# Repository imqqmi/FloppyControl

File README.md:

# FloppyControl

## Introduction
This project started in 2015. I had 300 floppy disks that I kept from my Amiga 500 and Amiga 1200 period. I planned to buy a second hand Amiga after I sold them for a new PC. That of course didn't happen. The data stored on the floppy disks was mostly my personal files, videos, music modules, painted pictures, 3D objects and renderings etc. And a complete backup of my system and data files. I wanted to reconstruct the files that I used to have. 

However, the Amiga disk format is not something any PC could read, at least not in Windows in a simple way. The disks were in a poor state with fungus and dust. So I set out to clean them. The 3D printable Floppy cleaning kit was a result of this. 

## This is the stategy I followed to get the most data without the risk of losing it:
- The most valuable data will be recovered once I can be certain the recovery proces is sound
- No captured data is thrown away. The first capture could be the best one because the disk may disintegrate/scratch during the capture process due to the disk surface letting loose.
- Extensive analysis is done to make sure that every opportunity is taken to get the data. This includes doing oscilloscope captures of the analoque flux signal, error correct and looking for duplicate data for reconstruction
- Low cost, off the shelve parts
- Windows application to control the hardware (C#)

## Status
This is the first commit of the project. I will call it version 1.0. It's capable of capturing Amiga and PC DOS disks and some variants of both. MSX disks for example are also supported. All disks can be captured, though not all disks can be decoded to a disk image yet. You could try adding your own.

## Hardware
The first version I made was based on a PIC16F1938 overclocked at 80MHz. An USB2RS232 donlge with a PL2303 chip was used at 5mbit/s.
The second (current) version uses a standard Arduino Due. I've designed a shield for it so it can easily be built. The native usb is used which eliminates the USB2RS232 dongle and makes things a lot more stable.

## Software
The real magic happens in the software that converts the flux transitions (or periods) into MFM, then into data and finally into sectors and disk images.

The following disk formats are supported:
- Double density and high density (720KB and 1.44MB) 3.5" disks
- 360KB 5.25" PCDOS disks.
- M2 special format for storing larger amounts of data
- AmigaDOS and Amiga DiskSpare disk formats. PFS is also supported since the format is similar to AmigaDOS.

File formats that can be imported:
- .bin files produces by FloppyControl App, a simple stream dump file format. Each byte contains a period of 2, 4, 6 or 8us. Timer tick frequency may vary.
- .SCP files can be imported
- .raw files from Kryoflux can be imported.

There are some experimental error correction functions in FloppyControl that allows you to do some analysis and limited error correction. It's still a very time consuming and manual process.

Other features include:
- Oscilloscope analogue flux transition capture support. At this point only the Rigol DS1054Z is supported and tested. Other scopes may work but it's not tested. Please let me know if it works. A modified floppy drive is needed for this. The oscilloscope should have at least 20MB storage to store a full track in memory.
- Oscilloscope captures can be edited so that errors can be corrected manually. A waveform editor is included. 
- The waveform can be converted into sector data using the processing capabilities (differential filtering, time based filtering, period conversion and data conversion).
- A sectormap shows you exactly the state of the capture and conversion. Bad sectors can be recaptured and existing data can be reprocessed with different settings, allowing you to 'scan' for good sectors in the dataset.
- All the graphs have some kind of interaction with them. 
  - The histogram can be clicked, this will activate automatic peak detection for the MFM processing. This will find the optimum settings for you.
  - The scatterplot will zoom in and out using the scroll wheel and you can drag to move the view to another location. For PC data, the periods can be edited (enable editing to avoid accidental changes). 
  - The Oscilloscope graphs can likewise be moved and zoomed. It has some advanced scaling routines to display the waveforms like an oscilloscope does, so you can see subpixel detail to find weak spots in the signal easier and faster.
  - The error correction map can be used to locate problem areas by overlaying two captures of the same sector (if the header is crc ok). This may help pinpointing the problem area and allows you to try automatic error correction (using guestimated brute force).
  - Error corrected sectors will be copied to the sector map.
  - There's some rudimentary multi threading support but it breaks in most cases. Try if it works, it'll speed up processing up to 3x on a quad core. 
  - FloppyControl uses a base folder in which the captures are stored. The Base filename is used to create a folder and naming the files inside that folder using a counter. It will never overwrite data (for .bin, .prj and dsk/adf files).
  - bin files with bad sectors can be saved as bad sectors only. This makes them much smaller for reprocessing and finding that illusive good sector.
  - You can choose 'bad sectors only' during processing. This does the same as saving just the bad sectors, it'll reduce the amount of data processed (all good sectors are skipped, they are found already so no point in reprocessing them).

The sources are released as GPL v3.0.

The firmware can be compiled using Arduino Studio v1.8.8.

The project makes use of DPLL class which is based on US patent 4,780,844 and written by DrCoolzic (Jean Louis-Guérin) and gracefully allowed me to inlcude it in this project. See the file DPLL.cs for more information.

The FloppyControl App can be compiled using Visual Studio 2015 or 2017 community edition. You may need to install VC redistributables to run the software as stand alone.

The PCB for the PIC and Arduino Due shield version is created in Eagle v7.3. Newer versions of eagle (free/community edition should work). 

Please let me know if you have any questions. Contributions to the project is appreciated. Please send the pull requests, I'll see if I can integrate them.

## More information

See my blog for more information:
http://www.makercentral.net

See videos about the use of FloppyControl App:
https://www.youtube.com/channel/UCJSWen8mcsrenXGCEr2fJ9w

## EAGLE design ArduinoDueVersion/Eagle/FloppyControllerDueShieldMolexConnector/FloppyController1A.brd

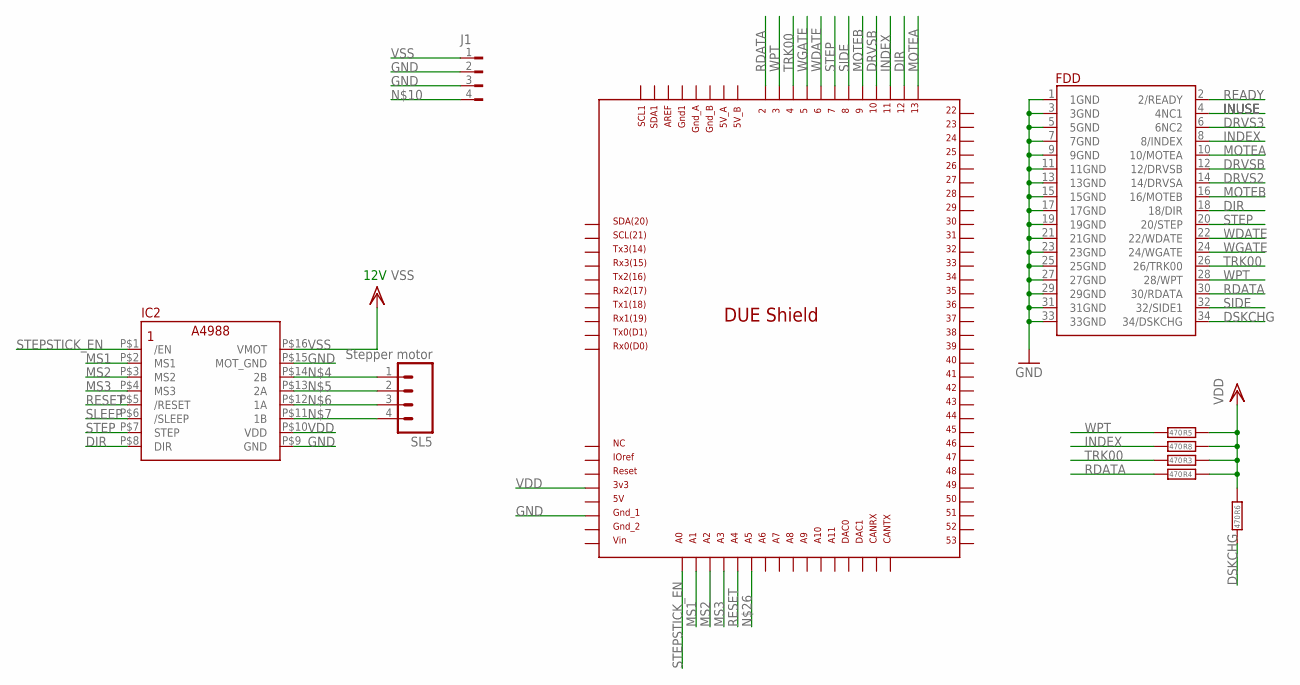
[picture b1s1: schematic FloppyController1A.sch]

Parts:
FDD: FLOPPY_34PIN_CONN; FLOPPY_34PIN_DUALROW
IC2: STEPSTICK_A4988
J1: FLOP-4W827001; 827001
R3, R4, R5, R6, R8: 470; M1206
SL5: Stepper motor; 04P
U$1: DUE(NOCONN); DUE(NORMAL_NO_CONN)

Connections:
DIR: FDD.18 (18/DIR), IC2.P$8 (DIR), U$1.12
DRVS2: FDD.14 (14/DRVSA)
DRVS3: FDD.6 (6NC2)
DRVSB: FDD.12 (12/DRVSB), U$1.10
DSKCHG: FDD.34 (34/DSKCHG), R6.1
GND: FDD.1 (1GND), FDD.3 (3GND), FDD.5 (5GND), FDD.7 (7GND), FDD.9 (9GND), FDD.11 (11GND), FDD.13 (13GND), FDD.15 (15GND), FDD.17 (17GND), FDD.19 (19GND), FDD.21 (21GND), FDD.23 (23GND), FDD.25 (25GND), FDD.27 (27GND), FDD.29 (29GND), FDD.31 (31GND), FDD.33 (33GND), IC2.P$9 (GND), IC2.P$15 (MOT_GND), J1.2, J1.3, U$1.GND_1
INDEX: FDD.8 (8/INDEX), R8.1, U$1.11
INUSE: FDD.4 (4NC1)
MOTEA: FDD.10 (10/MOTEA), U$1.13
MOTEB: FDD.16 (16/MOTEB), U$1.9
MS1: IC2.P$2 (MS1), U$1.A1
MS2: IC2.P$3 (MS2), U$1.A2
MS3: IC2.P$4 (MS3), U$1.A3
unnamed: IC2.P$14 (2B), SL5.1
unnamed: IC2.P$13 (2A), SL5.2
unnamed: IC2.P$12 (1A), SL5.3
unnamed: IC2.P$11 (1B), SL5.4
RDATA: FDD.30 (30/RDATA), R4.1, U$1.2
READY: FDD.2 (2/READY)
RESET: IC2.P$5 (/RESET), U$1.A4
SIDE: FDD.32 (32/SIDE1), U$1.8
SLEEP: IC2.P$6 (/SLEEP)
STEP: FDD.20 (20/STEP), IC2.P$7 (STEP), U$1.7
STEPSTICK_EN: IC2.P$1 (/EN), U$1.A0
TRK00: FDD.26 (26/TRK00), R3.1, U$1.4
VDD: IC2.P$10 (VDD), R3.2, R4.2, R5.2, R6.2, R8.2, U$1.3V3
VSS: IC2.P$16 (VMOT), J1.1
WDATE: FDD.22 (22/WDATE), U$1.6
WGATE: FDD.24 (24/WGATE), U$1.5
WPT: FDD.28 (28/WPT), R5.1, U$1.3

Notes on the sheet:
12V

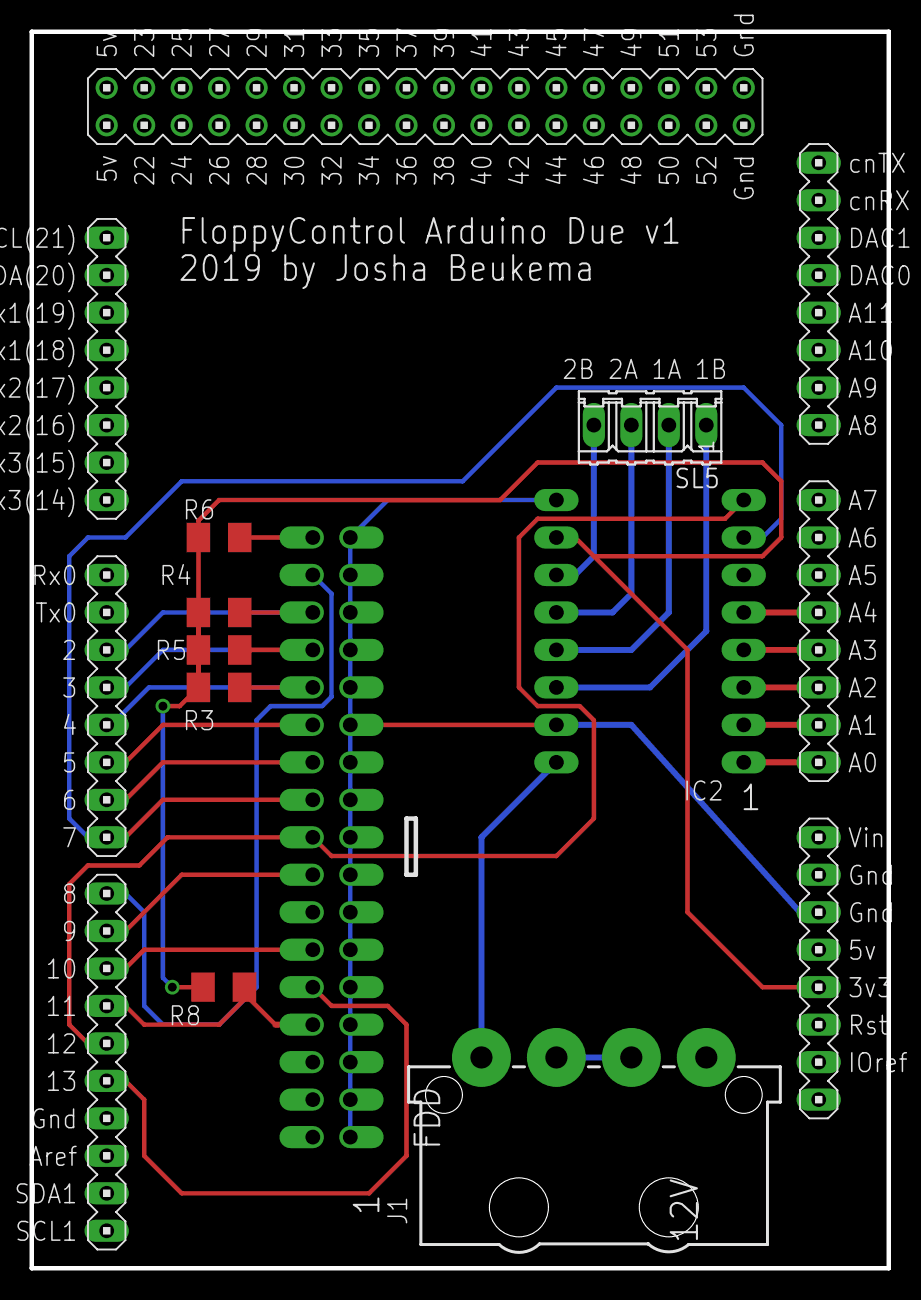
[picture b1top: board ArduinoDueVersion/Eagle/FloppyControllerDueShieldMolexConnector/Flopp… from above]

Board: 2 copper layers, 58.1 x 83.8 mm, 10 parts (0 on the bottom side), 25 nets.

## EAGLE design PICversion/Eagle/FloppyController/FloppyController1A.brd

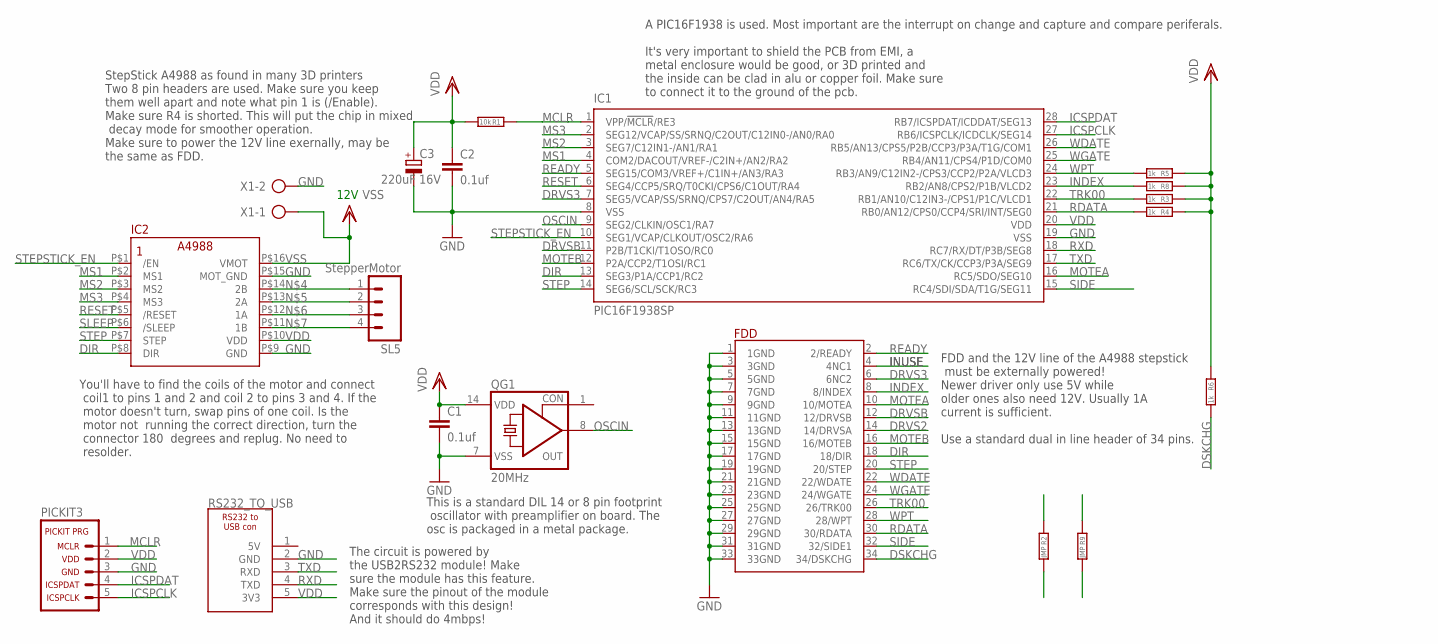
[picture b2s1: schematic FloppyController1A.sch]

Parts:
C1, C2: 0.1uf; C0805TOP
C3: 220uF 16V; E2,5-6
FDD: FLOPPY_34PIN_CONN; FLOPPY_34PIN_DUALROW
IC1: PIC16F1938SP; DIL28-3
IC2: STEPSTICK_A4988
PICKIT3: PICKIT3CONNECTOR; 05P
QG1: 20MHz; SG51
R1: 10k; M1206
R2, R9: JMP; M1206
R3, R4, R5, R6, R8: 1k; M1206
RS232_TO_USB: RS232_TO_USB_CONNECTOR; 05P
SL5: StepperMotor; 04P
X1: AK500/2-H

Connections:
DIR: FDD.18 (18/DIR), IC1.13 (SEG3/P1A/CCP1/RC2), IC2.P$8 (DIR)
DRVS2: FDD.14 (14/DRVSA)
DRVS3: FDD.6 (6NC2), IC1.7 (SEG5/VCAP/SS/SRNQ/CPS7/C2OUT/AN4/RA5)
DRVSB: FDD.12 (12/DRVSB), IC1.11 (P2B/T1CKI/T1OSO/RC0)
DSKCHG: FDD.34 (34/DSKCHG), R6.1
GND: C1.2, C2.2, C3.-, FDD.1 (1GND), FDD.3 (3GND), FDD.5 (5GND), FDD.7 (7GND), FDD.9 (9GND), FDD.11 (11GND), FDD.13 (13GND), FDD.15 (15GND), FDD.17 (17GND), FDD.19 (19GND), FDD.21 (21GND), FDD.23 (23GND), FDD.25 (25GND), FDD.27 (27GND), FDD.29 (29GND), FDD.31 (31GND), FDD.33 (33GND), IC1.8 (VSS), IC1.19 (VSS), IC2.P$9 (GND), IC2.P$15 (MOT_GND), PICKIT3.3 (3_GND), QG1.7 (VSS), R9.1, R9.2, RS232_TO_USB.2 (GND), X1.2
ICSPCLK: IC1.27 (RB6/ICSPCLK/ICDCLK/SEG14), PICKIT3.5 (5_ICSPCLK)
ICSPDAT: IC1.28 (RB7/ICSPDAT/ICDDAT/SEG13), PICKIT3.4 (4_ICSPDAT)
INDEX: FDD.8 (8/INDEX), IC1.23 (RB2/AN8/CPS2/P1B/VLCD2), R8.1
INUSE: FDD.4 (4NC1)
MCLR: IC1.1 (VPP/!MCLR!/RE3), PICKIT3.1 (1_MCLR), R1.2
MOTEA: FDD.10 (10/MOTEA), IC1.16 (RC5/SDO/SEG10), R2.1, R2.2
MOTEB: FDD.16 (16/MOTEB), IC1.12 (P2A/CCP2/T1OSI/RC1)
MS1: IC1.4 (COM2/DACOUT/VREF-/C2IN+/AN2/RA2), IC2.P$2 (MS1)
MS2: IC1.3 (SEG7/C12IN1-/AN1/RA1), IC2.P$3 (MS2)
MS3: IC1.2 (SEG12/VCAP/SS/SRNQ/C2OUT/C12IN0-/AN0/RA0), IC2.P$4 (MS3)
unnamed: IC2.P$14 (2B), SL5.1
unnamed: IC2.P$13 (2A), SL5.2
unnamed: IC2.P$12 (1A), SL5.3
unnamed: IC2.P$11 (1B), SL5.4
OSCIN: IC1.9 (SEG2/CLKIN/OSC1/RA7), QG1.8 (OUT)
RDATA: FDD.30 (30/RDATA), IC1.21 (RB0/AN12/CPS0/CCP4/SRI/INT/SEG0), R4.1
READY: FDD.2 (2/READY), IC1.5 (SEG15/COM3/VREF+/C1IN+/AN3/RA3)
RESET: IC1.6 (SEG4/CCP5/SRQ/T0CKI/CPS6/C1OUT/RA4), IC2.P$5 (/RESET)
RXD: IC1.18 (RC7/RX/DT/P3B/SEG8), RS232_TO_USB.4 (TXD)
SIDE: FDD.32 (32/SIDE1), IC1.15 (RC4/SDI/SDA/T1G/SEG11)
SLEEP: IC2.P$6 (/SLEEP)
STEP: FDD.20 (20/STEP), IC1.14 (SEG6/SCL/SCK/RC3), IC2.P$7 (STEP)
STEPSTICK_EN: IC1.10 (SEG1/VCAP/CLKOUT/OSC2/RA6), IC2.P$1 (/EN)
TRK00: FDD.26 (26/TRK00), IC1.22 (RB1/AN10/C12IN3-/CPS1/P1C/VLCD1), R3.1
TXD: IC1.17 (RC6/TX/CK/CCP3/P3A/SEG9), RS232_TO_USB.3 (RXD)
VDD: C1.1, C2.1, C3.+, IC1.20 (VDD), IC2.P$10 (VDD), PICKIT3.2 (2_VDD), QG1.14 (VDD), R1.1, R3.2, R4.2, R5.2, R6.2, R8.2, RS232_TO_USB.5 (3V3)
VSS: IC2.P$16 (VMOT), X1.1
WDATE: FDD.22 (22/WDATE), IC1.26 (RB5/AN13/CPS5/P2B/CCP3/P3A/T1G/COM1)
WGATE: FDD.24 (24/WGATE), IC1.25 (RB4/AN11/CPS4/P1D/COM0)
WPT: FDD.28 (28/WPT), IC1.24 (RB3/AN9/C12IN2-/CPS3/CCP2/P2A/VLCD3), R5.1

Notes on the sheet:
StepStick A4988 as found in many 3D printers Two 8 pin headers are used. Make sure you keep them well apart and note what pin 1 is (/Enable). Make sure R4 is shorted. This will put the chip in mixed decay mode for smoother operation. Make sure to power the 12V line exernally, may be the same as FDD.
12V
FDD and the 12V line of the A4988 stepstick must be externally powered! Newer driver only use 5V while older ones also need 12V. Usually 1A current is sufficient. Use a standard dual in line header of 34 pins.
The circuit is powered by the USB2RS232 module! Make sure the module has this feature. Make sure the pinout of the module corresponds with this design! And it should do 4mbps!
You'll have to find the coils of the motor and connect coil1 to pins 1 and 2 and coil 2 to pins 3 and 4. If the motor doesn't turn, swap pins of one coil. Is the motor not running the correct direction, turn the connector 180 degrees and replug. No need to resolder.
This is a standard DIL 14 or 8 pin footprint oscillator with preamplifier on board. The osc is packaged in a metal package.
A PIC16F1938 is used. Most important are the interrupt on change and capture and compare periferals. It's very important to shield the PCB from EMI, a metal enclosure would be good, or 3D printed and the inside can be clad in alu or copper foil. Make sure to connect it to the ground of the pcb.

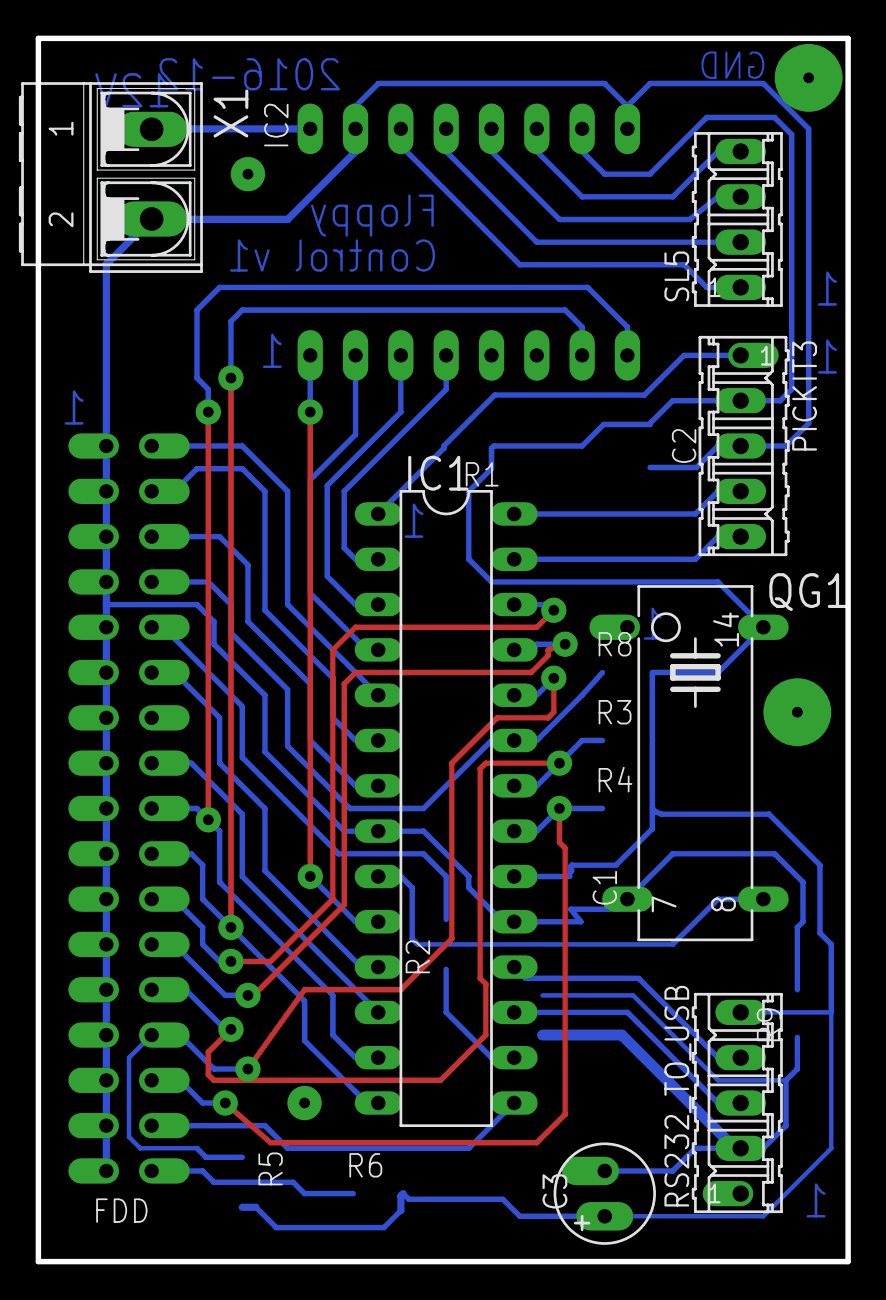
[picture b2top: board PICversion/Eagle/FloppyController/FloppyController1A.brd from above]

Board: 2 copper layers, 45.4 x 68.6 mm, 19 parts (0 on the bottom side), 33 nets.

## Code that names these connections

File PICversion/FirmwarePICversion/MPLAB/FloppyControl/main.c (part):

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 * LabPSU v1
 */

// Pins 27/28 = RB6/RB7 = DAT/CLK, not to be used for other purposes.
// pins 17/RC6 = TX, pin 18/RC7 = RX

#include <xc.h>
#include <stdio.h>
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#pragma config PLLEN = ON       // Phase locked loop off
#pragma config WDTE = SWDTEN    // Watchdog Timer Enable (WDT disabled)
#pragma config PWRTE = OFF      // Power-up Timer Enable (PWRT disabled)
#pragma config MCLRE = OFF      // MCLR Pin Function Select (MCLR/VPP pin function is digital input)
#pragma config CP = OFF         // Flash Program Memory Code Protection (Program memory code protection is disabled)
#pragma config CPD = OFF        // Data Memory Code Protection (Data memory code protection is disabled)
#pragma config BOREN = OFF      // Brown-out Reset Enable (Brown-out Reset disabled)
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#define OUT             0

// Outputs
#define MOTEB           LATC0
#define DRVSB           LATC1
#define MOTEA           LATC5


#define DIR             LATC2
#define STEP            LATC3
#define SIDE            LATC4
#define SELECT0         LATC5
#define _STEPSTICKEN    LATA6
#define MS1             LATA2 
#define MS2             LATA1 
#define MS3             LATA0 
#define WDATE           LATB5
#define WGATE           LATB4
#define RESET           LATA4

//Inputs, IOC
#define RDATA           PORTBbits.RB0   
#define RDATAIE         INTE
#define TRK00           PORTBbits.RB1
#define INDEX           PORTBbits.RB2   
#define READY           PORTAbits.RA3
//#define INUSE           PORTAbits.RA4


#define DATASIZE        256
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char recvchar=0;
char data[DATASIZE];
char buf[10];
char index=0;
char indexchanged = 0;
char trk00 = 0;
char curtrk = 0; // an attempt at keeping track of the current track
unsigned long rdatacount = 0; // I used this to try to count the pulses but longs took too long ;)
char tmr = 0; // stores the timer0 value at the start of the isr
char getdata =0; // instructs the ISR to start capturing the data.
volatile unsigned char datacnt = 0; // index for the data[] buffer, in ram for now.
char readbyte = 0; // holds the current byte we're reading
char readbytecnt = 0; // counts pairs of bits so we know when we've got a full byte
char readerr = 0;
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    unsigned char x; // tempbuf counter

    //Setup serial
    // pin 17/RC6 = TX, pin 18/RC7 = RX
    SPBRGH = 0;
    SPBRGL = BRGVAL;    // For 32Mhz and baudrate 117600
    SYNC = 0;       // Setup for asynchronous comm.
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    OPTION_REG = 0b00001000;

    //Capture configuration
    //CCP1SEL = 1; //CCP1 on RB0/RDATA
    CCP4CON = 0b00000100; // Capture every falling edge = 0b0000100, rising = 0b0000101
    PIE3bits.CCP4IE = 0;
    PIR3bits.CCP4IF = 0;
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    MS2 = 1;
    MS3 = 0;
    
    WGATE = 1;
    WDATE = 1;

    stop = 1;
    while(1) 
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
            case 'q': // Deselect drive
                //txstring("x12 DRVSB enabled\r\n\0");
                DRVSB = 1;
                SELECT0 = 1;
                RESET = 0;
            break;
            case 'w': // Disable  motor
                //txstring("16 MOTEB enabled\r\n");
                MOTEB = 1;
                _STEPSTICKEN = 1;
            break; 
            case 'e': // DIR = 1
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//**************************************************************
            case 'a': // Select drive
                //txstring("12 DRVSB disabled\r\n");
                DRVSB = 0;
                SELECT0 = 1;
                RESET = 1;
            break;
            case 's': // Enable motor and stepstick
                //txstring("16 MOTEB disabled\r\n");
                MOTEB = 0;
                MOTEA = 0;
                _STEPSTICKEN = 0;
            break;
            case 'd': // DIR = 0
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            break;
            case 'h': // HEAD 0
                
                SIDE = 1;

            break;
            case 'j': // HEAD 1
                
                SIDE = 0;

            break;
            case '[':
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{
    int i,j;
    
    DIR = 1; // decrement until trk00 is found
    
    // Set the microstepping to full step
    MS1 = 0;
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    unsigned int number_of_steps;
    unsigned int cnt;

    DIR = 1; // decrement until trk00 is found
    
    // Home head to track 00
    seektrk00();
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
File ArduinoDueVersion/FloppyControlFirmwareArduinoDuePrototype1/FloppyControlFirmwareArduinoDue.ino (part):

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    d/e forward/backward direction of the drive head
    f/r active low/high step signal
    t/g next track (single STEP=0/STEP=1 combination)/previous track
    j/h side=0/side=1
    ./, stop capture/start capture
    [/] increment/decrement microstepping for step stick
    y   next track based on microstepping
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// necessary. MOTEA and MOTEB are both needed to make sure it doesn't depend on the cable twist or no twist.

// Outputs                floppy connector  Needed only for reading
#define MOTEA           3 // p10            y
#define DRVSB           4 // p12            y
#define MOTEB           5 // p16            y

#define DIR             6 // p18            y
#define STEP            7 // p20            y
#define WDATE           12// p22
#define WGATE           13// p24
#define SIDE            8 // p32            y

//Inputs, IOC
#define READY           59 // p2
#define INDEX           10 // p8            y  
#define TRK00           11 // p26           y
#define WPT             9  // p28
#define RDATA           2  // p30           y
#define DSKCHG          60 // p34

// The stepstick is optional, allows you do read between tracks with microstepping.
// When you've glued disk donut back to the metal hub, the disk donut may be off center.
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  buf1ready = false;
  pinMode( LED_BUILTIN, OUTPUT);
  // Outputs
  pinMode( MOTEA, OUTPUT);
  pinMode( DRVSB, OUTPUT);
  pinMode( MOTEB, OUTPUT);
  pinMode( DIR, OUTPUT);
  pinMode( STEP, OUTPUT);
  pinMode( SIDE, OUTPUT);
  
  //Inputs, IOC
  pinMode( READY , INPUT);
  pinMode( INDEX , INPUT); // interrupt on change pin
  pinMode( TRK00, INPUT);
  pinMode( RDATA, INPUT); // Capture period times
  //Stepstick outputs
  pinMode( _STEPSTICKEN, OUTPUT);
  pinMode( MS1, OUTPUT);
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  setMS();

  //Turn off disk drive
  digitalWrite( DRVSB, 1); // DRVSB = 1;
  digitalWrite( RESET, 0); //RESET = 0;
  digitalWrite( MOTEA, 1); //MOTEB = 1;
  digitalWrite( MOTEB, 1); //MOTEB = 1;
  
  SerialUSB.begin(0);
  while (!SerialUSB);
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
            case 'q': // Deselect drive
                //txstring("x12 DRVSB enabled\r\n\0");
                digitalWrite( DRVSB, 1); // DRVSB = 1;
                //digitalWrite( MOTEA, 1); //SELECT0 = 1;
                digitalWrite( RESET, 0); //RESET = 0;
            break;
            case 'w': // Disable  motor
                //txstring("16 MOTEB enabled\r\n");
                digitalWrite( MOTEA, 1); //MOTEB = 1;
                digitalWrite( MOTEB, 1); //MOTEB = 1;
                digitalWrite( _STEPSTICKEN, 1); //_STEPSTICKEN = 1;
            break; 
            case 'e': // DIR = 1
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//**************************************************************
            case 'a': // Select drive
                //txstring("12 DRVSB disabled\r\n");
                digitalWrite( DRVSB, 0); //DRVSB = 0;
                //digitalWrite( MOTEA, 1); //SELECT0 = 1;
                digitalWrite( _STEPSTICKEN, 1); //RESET = 1;
            break;
            case 's': // Enable motor and stepstick
                //txstring("16 MOTEB disabled\r\n");
                digitalWrite( MOTEB, 0); //MOTEB = 0;
                digitalWrite( MOTEA, 0); //MOTEA = 0;
                digitalWrite( _STEPSTICKEN, 0); //_STEPSTICKEN = 0;
            break;
            case 'd': // DIR = 0
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            break;
            case 'h': // HEAD 0
                
                digitalWrite( SIDE, 1); //SIDE = 1;

            break;
            case 'j': // HEAD 1
                
                digitalWrite( SIDE, 0); //SIDE = 0;

            break;
            case '[':
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{
    int i,j;
    
    digitalWrite( DIR, 1); //DIR = 1; // decrement until trk00 is found

    // Set the microstepping to full step
    digitalWrite( MS1, 0); // MS1 = 0;
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    unsigned int number_of_steps;
    unsigned int cnt;

    digitalWrite( DIR, 1); //DIR = 1; // decrement until trk00 is found
    
    // Home head to track 00
    seektrk00();
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
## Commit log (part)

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2019-03-04 Added the cleaning kit and PIC firmware version.
2019-03-04 Adding the new firmware using Arduino Due and the Windows FloppyControl App
2019-03-04 Adding back the folders.
2019-03-04 Removed some debugging output. Fixed goto track in DirectMode.
2019-03-05 Added eagle Arduino Due shield library. Added some pin assigments.
2019-03-05 Some more array index overrup or underrun bug fixed.
2019-03-09 Removed static properties from FDDProcessing class. Fixed the Reset output function. I now displose of the processing while keeping rxbuf.
2019-03-09 Added versioning. Catched an out of memory exception.
2019-03-09 Fixed some bugs when resetting output. The scatterplot couldn't move backwards.
2019-03-09 Moved load/save project files to fileio class. Moved some error correction methods.
2019-03-10 Created Oscilloscope class and moved all code from FloppyControlApp. Moved more stuff file related.
2019-03-10 Renamed Oscilloscope class to WaveformEdit. Fixed a bug that didn't allow to click om crcok amigados sectors showing location in scatterplot.
2019-03-10 Disconnect before resetting the output.
2019-03-12 Fixed an issue with inconsistent TRK00 finding, giving it a wrong offset sometimes, reading between tracks instead. Stepstick not working bug fixed.
2019-03-14 Gui redesign. Broken histogram.
2019-03-15 Stable v1.0
2019-03-15 Persist settings across Quick and capture/processing tabs.
2019-03-15 Bytes received is now set when opening files.
2019-03-16 Improving track finding accuracy
2019-03-17 Proof of concept now works with microstepping and GotoTrack.
2019-03-17 New track handling has been integrated into FDDCapture and is working.
2019-03-17 Added Gui mode options basic, advanced and dev.
2019-03-17 Optimized processing. It was reporocessing already processed data, it's skipping that now improving scanning performance a great deal, it was slowing down previously. Bytes per second capture now sho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
2019-03-21 After capture the buffer isn't large enough for scanning. Fixed. It will now increase the buffer by 10MB when needed.
2019-03-23 Out of memory handling added.
2019-03-24 Fixed release 1.1.0 merge
2019-03-30 Fixed bug in limit t/s. Added image to Quick tab. Set active control on startup. Added right click menu in sectormap: 1 second capture, limit to t/s. Added explore here button.
2019-03-31 Fixed bugs in the export trimmed data method. Due to noise it may be that previously recoverable period data doesn't read immeidately anymore due to the order in which noise and data is placed one af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
2019-04-03 Fixed capture timer. Fixed scatterplot graph printing track/sector labels header/data overlapping.
2019-04-04 Added pictures of the arduino due shield pcb.
2019-04-10 Cleanup. Increased polling for serial port to improve data transfer. Moved National Instruments dll files so you don't have to install the complete dev kit.
2019-04-11 Fixed the progress bar. Added a getting started guide.
2019-04-11 Getting started added.
2020-12-13 Fix SCP load exception.
2020-12-13 Added file > close. Some event cleanup.
2020-12-13 Fix sector viewer out of bounds error.
2023-03-28 Reversed deep scan buffer size direction, more likely to find correct sectors.
2023-03-28 Refactoring, splitting multiple classes in a single file to multiple files.
2023-03-28 Added specific deep scan for Adaptive1. This skips the RateOfChange scan which is a variable that's not used with this processing type.
2023-03-28 Refactored Adaptive2 to its own file to improve readability.
2023-03-28 Refactor adaptive1.
2023-03-28 Refactor Normal processing type.
2023-03-28 Refactored Aufit process type.
2023-05-02 Enable multithreading support again.
2023-05-02 Cleanup, prevent exception.
2023-05-02 Moved callback methods and keyboard shortcut handler to FormHelper class. Moved variables/properties as well and model classes.
2023-05-02 Moved methods, added regions to group methods.
2023-05-02 Cleanup. Fixed unhandled exceptions in graphics library.
2023-05-02 Cleanup and moved error correcting methods to its own file.
2023-05-02 Fixed not being able to edit waveform after loading from disk. After capture wasn't affected.
2023-05-03 Added comment about design choice for drawing in scope captured waveform.
2023-05-03 Flattened nested if statements.
2023-05-10 Better default value for random function to find good sectors with flux transitions that are just on the edge of being correct.
2023-05-10 Restore rate of change value after scan.
2023-05-10 Set threads that were created to null and reset threads at the start so that these are recreated. Now if for a second time processing is started with threads > 1 it will use that number of threads/co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
2023-05-15 Upgrade to .net 4.7.2
2023-05-16 Made converting MFM to a byte array generic and refactored it into the PC processing method. This also improved variable naming, ie bytebuf vs Idam and SectorBlock, and improved memory usage as the a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
2023-05-16 Removed unused variables.
2023-05-16 Reversed suppressing some warnings.
2023-05-16 Silence set read only modifier.
2023-05-16 Rename and cleanup unused variables and assignments.
2023-05-16 More cleanup.
2023-05-17 Moved validation of header to separate methods.
2023-05-17 Moved calculation of disk image sector offset, and renamed it for better clarity.
2023-05-17 replaced for() loop with Array.Copy which is considerably faster.
2023-05-17 Commented on non thread safe.
2023-05-17 Moved Method down.
2023-05-18 More moving to methods with proper names making it much more clear what is going on. Added comments. Moved stuff around that made more sense when things that belong together are close to each other e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
2023-05-18 When a sector is already CrcOk and other data of the same sector is found it isn't processed to improve performance. These entries must be omitted since they don't contain any data for error correcti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
2023-05-18 Moved methods to more sensible order. Some more cleanup.
2023-05-19 Experimental methods added: Added entropy based splicing of captured sectors to put together all the best signals into one period stream to try to recover data. Added average function to do the same.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
2023-05-19 Fixed issues with the scatterplot on the error correction tab, it will now display the full sector period data when changing the selected list item. Also labels are now offset in the scatterplot and 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
2023-05-22 Added a copy of the project that converts the application to dotnet7.
2023-05-22 Create new unit test project compatible with .net7 and fix unit tests.
2023-05-22 Improved unit test speed for PC. Aligned Amiga peaks properly so that 1300 for adapt track can be used.
2023-05-22 Fixed some scaling issues with the scatterplot and it seemed to skip when moving around with click and drag.
2023-05-23 Added class descriptions and moved crc32 class to utility namespace.
2023-05-23 Split and moved files with multiple classes and models. Removed public enum InitialCrcValue from one location as it was a duplicate.
2023-05-23 More moving around of classes into namespaces and class files.
2023-05-23 Update scatterplot after processing since entropy is updated.
2023-05-23 The peaks threshold sliders were shifted after the upgrade to .net 7. I've moved them about 100px.
2023-05-24 Amiga processing cleanup and optimization.
2023-05-24 See complete sector with header when clicking on the sectormap, not the sector data and next header.
2023-05-24 Clicking on the sectormap, pc bad sectors failed to show on the scatterplot, fixed. Both Amiga and PC sectors work.
2023-05-24 Fixed an issue that Amiga data didn't show in sector data textbox, in fact, no data to disk image was written.
2023-05-24 Fixed saving trimmed period data to only include the good sectors for PC. The rest is not yet working ie PC bad sectors, Amiga good and bad sectors.
2023-05-24 removed more logging that's no longer needed. Store window size in settings and restore size when starting.
2023-05-25 Moved error correction stuff to its own class for PC error correction. Realigning PC MFM data is working again, selecting the start point was broken.
2023-05-25 Moved Aligning mfm data to a separate method.
2023-05-25 Bug: Average works only if the whole list is selected, will be fixed soon. Added bitshift control, not sure if the bitshift is calculated correctly all the time, going to experiment with it for a whi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
2023-05-25 More conversions to long.
2023-05-30 Fixed an issue with the first detected sector not setting sectorspertrack, resulting data being saved to the wrong sector. It's rare but does happen.
2023-05-30 Added warning of sectorspertrack wasn't set to be sure I know when it's going wrong. It shouldn't be possible but still.
2023-05-31 Error correction scanning for amigados.
2023-05-31 Skip already saved track/sector.
2023-06-14 Bump Microsoft.Windows.Compatibility
    Bumps [Microsoft.Windows.Compatibility](https://github.com/dotnet/runtime) from 7.0.1 to 7.0.3.
    - [Release notes](https://github.com/dotnet/runtime/releases)
    - [Commits](https://github.com/dotnet/runtime/compare/v7.0.1...v7.0.3)
    ---
    updated-dependencies:
    - dependency-name: Microsoft.Windows.Compatibility
2023-07-17 On capture, a few recoverable exceptions were thrown. Checking some bounds and the error is fixed.
2024-09-17 Example waveform file that can be opened on the waveform editor tab.
2025-01-08 Change "us" unit in strings and comments to proper "µs"
2025-01-08 Use before initialize fix.
2026-01-26 Added controls for the extract file per bad sector feature.
2026-01-26 Phase 1 Items 1-2: Add DskX.Core integration and Stream support
    - Item 1: Add DskX.Core project reference to FloppyControlApp.csproj
    - Item 2: Extend DiskImageReader to accept Stream (MemoryStream) input
    - Add Open(Stream) method overload
    - Implement stream ownership tracking (_ownsStream flag)
    - Only dispose streams that we own (file-based), not external streams
    - Allows FloppyControlApp to pass in-memory disk images for FAT12 analysis
2026-01-26 docs: Update Phase 1 execution plan - Items 1-3 complete
2026-01-26 Phase 1 Item 5: Implement LoadFilesButton event handler
    Add LoadFilesButton click handler to read FAT12 filesystem and populate file list:
    - Add _diskImageFiles field to FloppyControl class
    - Implement LoadFilesButton_Click() to initialize DiskImageFiles and populate combobox
    - Implement IsPCDiskFormat() helper to check for PC DOS formats
    - Wire up event handler in Designer
    - Show user feedback with file count and error messages
2026-01-26 Phase 1 Item 7: Implement ExportFilesButton handler
    Add file export functionality with bad sector substitution:
    - ExportFilesButton_Click(): Main handler for exporting file variations
    - BackupSectorData(): Saves original sector data before modifications
    - SubstituteSectorData(): Substitutes bad sector candidate into disk array
    - RestoreSectorData(): Restores original data after extraction
    - ExtractFileFromDisk(): Wrapper for DiskImageFiles.ExtractFile()
2026-01-26 docs: spec for adding track/sector visualization of PC disk files covering what sectors. And export files with different bad sectors to find what gives best recovery/restoration options.
2026-01-26 Update Phase 1 exec plan: Item 8 complete with commit hash
